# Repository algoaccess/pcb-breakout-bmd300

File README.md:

# pcb-breakout-bmd300

Pin breakout of the Rigado BMD-300 module based on Nordic NRF52 to through-hole pin headers for prototyping.

##PCB Design software and addons used

1. Eagle 7.5.0 standard but freeware should work too
2. BMD-300 library by [Rigado](https://www.rigado.com/product/bmd-300/) (in repo as BMD-300.lbr)

##Images

This is the Rev 1 version where there is an error in Rigado's library between Pin 30 and 31 as raised by this issue [here](https://github.com/algoaccess/pcb-breakout-bmd300/issues/1). I have updated to the lastest library by Rigado in Rev 2.

##Schematic drawings
Images are exported from Eagle at 600dpi.

##Parts required

The BMD-300 is still currently sampling and can be requested direct from the manufacturer [Rigado](https://www.rigado.com/product/bmd-300/)

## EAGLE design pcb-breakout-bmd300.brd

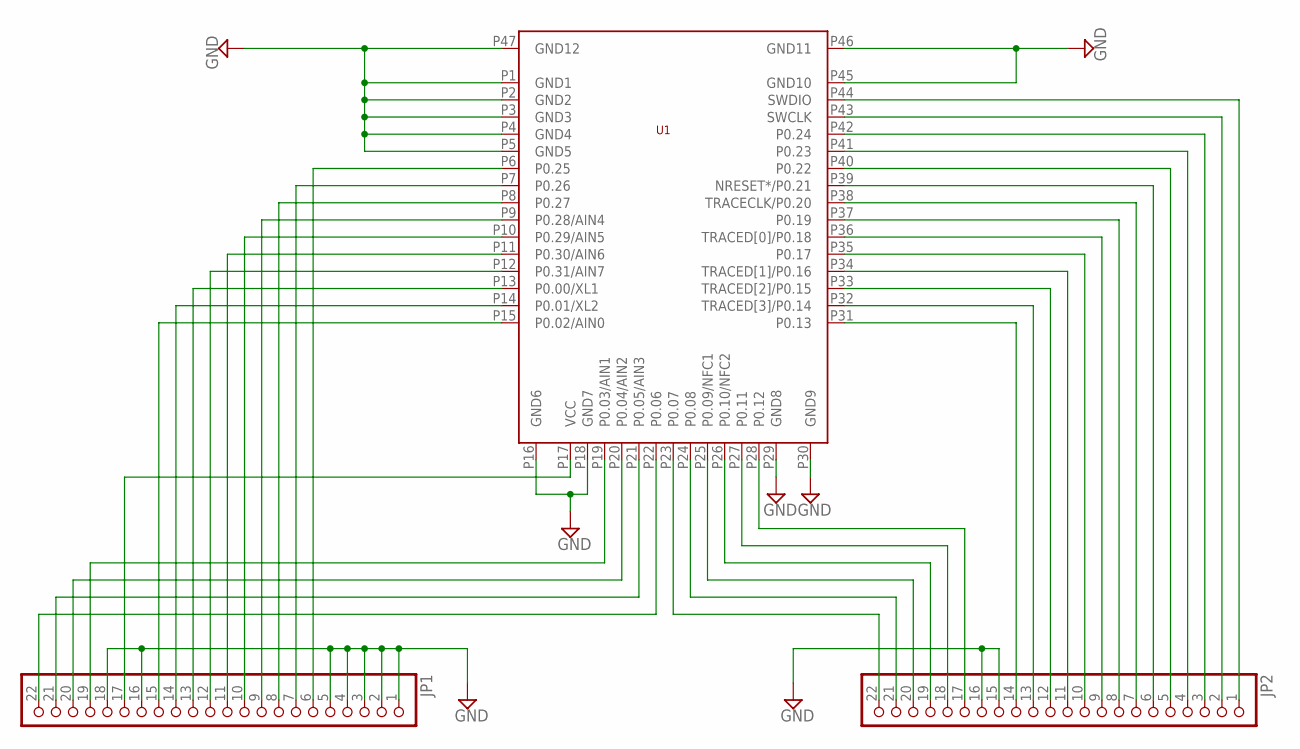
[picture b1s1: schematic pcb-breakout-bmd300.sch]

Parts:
JP1, JP2: PINHD-1X22; 1X22
U1: BMD-300

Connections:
GND: JP1.1, JP1.2, JP1.3, JP1.4, JP1.5, JP1.16, JP1.18, JP2.15, JP2.16, U1.P1 (GND1), U1.P2 (GND2), U1.P3 (GND3), U1.P4 (GND4), U1.P5 (GND5), U1.P16 (GND6), U1.P18 (GND7), U1.P29 (GND8), U1.P30 (GND9), U1.P45 (GND10), U1.P46 (GND11), U1.P47 (GND12)
unnamed: JP1.6, U1.P6 (P0.25)
unnamed: JP1.7, U1.P7 (P0.26)
unnamed: JP1.8, U1.P8 (P0.27)
unnamed: JP1.9, U1.P9 (P0.28/AIN4)
unnamed: JP1.10, U1.P10 (P0.29/AIN5)
unnamed: JP1.11, U1.P11 (P0.30/AIN6)
unnamed: JP1.12, U1.P12 (P0.31/AIN7)
unnamed: JP1.13, U1.P13 (P0.00/XL1)
unnamed: JP1.14, U1.P14 (P0.01/XL2)
unnamed: JP1.15, U1.P15 (P0.02/AIN0)
unnamed: JP1.17, U1.P17 (VCC)
unnamed: JP1.19, U1.P19 (P0.03/AIN1)
unnamed: JP1.20, U1.P20 (P0.04/AIN2)
unnamed: JP1.21, U1.P21 (P0.05/AIN3)
unnamed: JP1.22, U1.P22 (P0.06)
unnamed: JP2.22, U1.P23 (P0.07)
unnamed: JP2.21, U1.P24 (P0.08)
unnamed: JP2.20, U1.P25 (P0.09/NFC1)
unnamed: JP2.19, U1.P26 (P0.10/NFC2)
unnamed: JP2.18, U1.P27 (P0.11)
unnamed: JP2.17, U1.P28 (P0.12)
unnamed: JP2.14, U1.P31 (P0.13)
unnamed: JP2.13, U1.P32 (TRACED[3]/P0.14)
unnamed: JP2.12, U1.P33 (TRACED[2]/P0.15)
unnamed: JP2.11, U1.P34 (TRACED[1]/P0.16)
unnamed: JP2.10, U1.P35 (P0.17)
unnamed: JP2.9, U1.P36 (TRACED[0]/P0.18)
unnamed: JP2.8, U1.P37 (P0.19)
unnamed: JP2.7, U1.P38 (TRACECLK/P0.20)
unnamed: JP2.6, U1.P39 (NRESET*/P0.21)
unnamed: JP2.5, U1.P40 (P0.22)
unnamed: JP2.4, U1.P41 (P0.23)
unnamed: JP2.3, U1.P42 (P0.24)
unnamed: JP2.2, U1.P43 (SWCLK)
unnamed: JP2.1, U1.P44 (SWDIO)

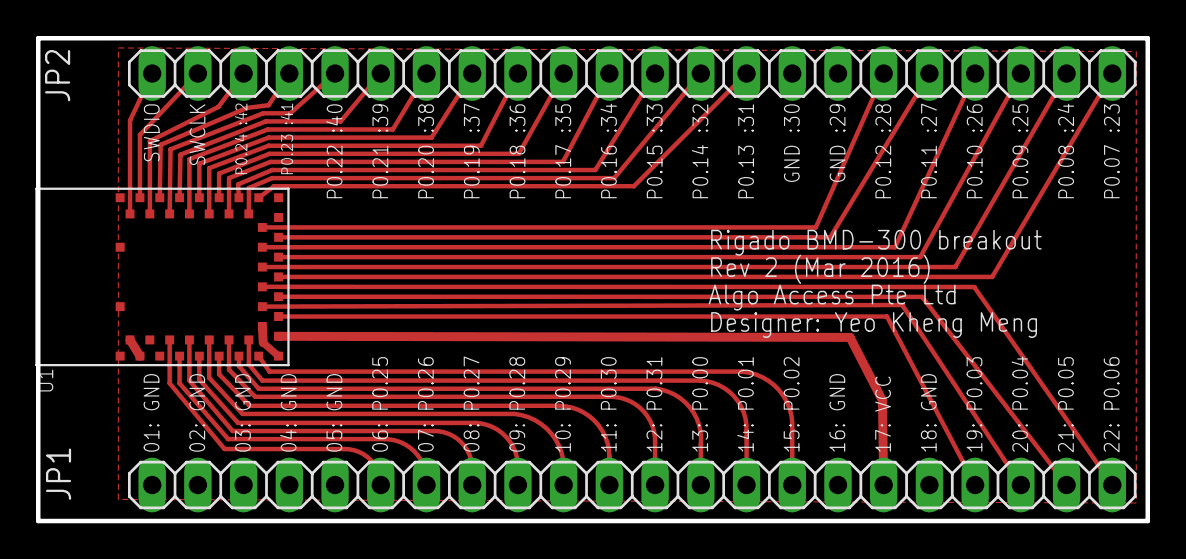
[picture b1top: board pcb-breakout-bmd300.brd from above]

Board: 2 copper layers, 61.6 x 26.8 mm, 3 parts (0 on the bottom side), 36 nets.

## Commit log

2016-01-27 label rename
2016-01-27 rev 1 gerber
2016-01-27 images
2016-02-05 front image
2016-03-12 Downloaded updated Eagle library from Rigado. Thanks to issue created here. https://github.com/algoaccess/pcb-breakout-bmd300/issues/1
2016-03-12 rev 2 gerbels
2016-04-04 update image to rev2
